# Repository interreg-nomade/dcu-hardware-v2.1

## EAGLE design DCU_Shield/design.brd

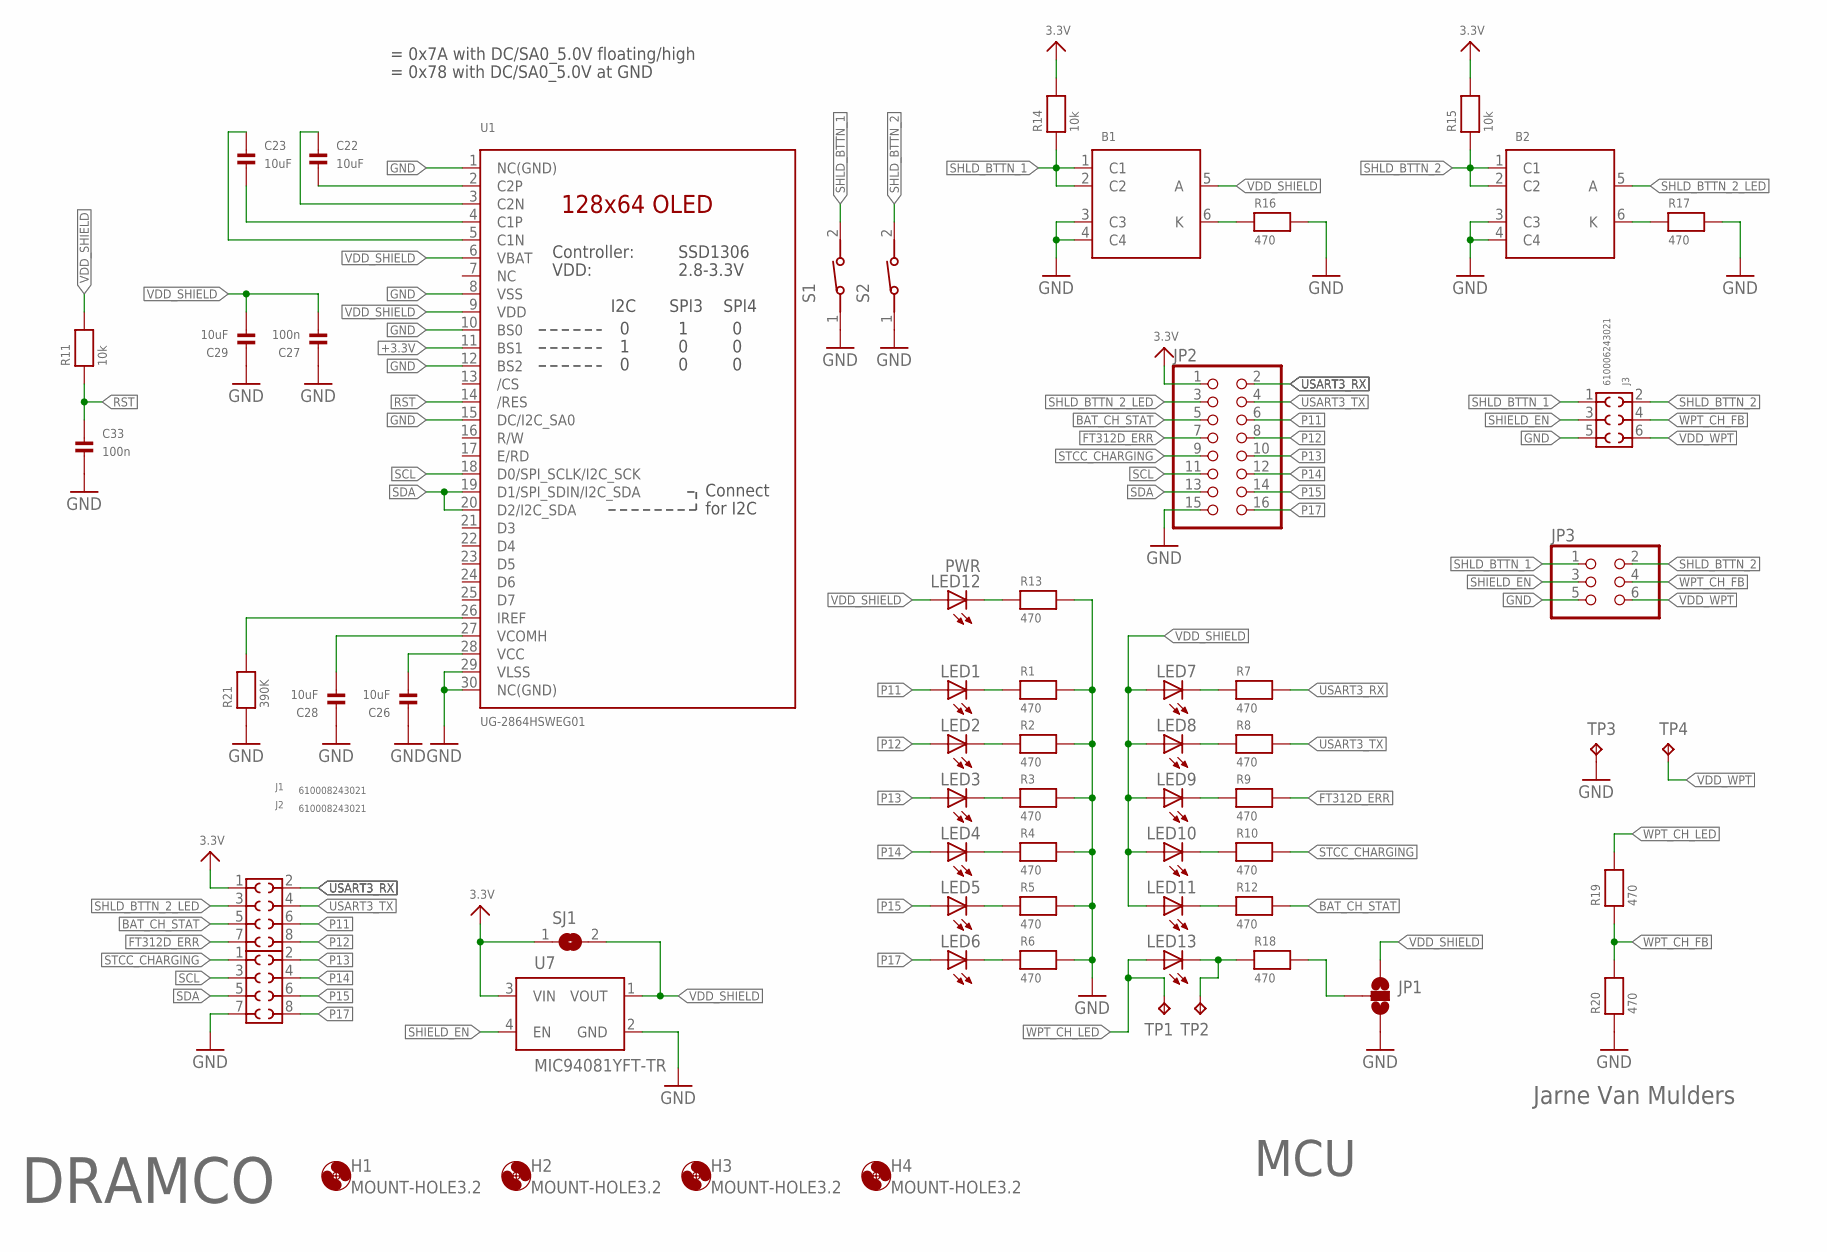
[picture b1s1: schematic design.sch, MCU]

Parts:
B1, B2: TS121273
C22, C23, C26, C28, C29: 10uF; 0805
C27, C33: 100n; 0603
H1, H2, H3, H4: MOUNT-HOLE3.2; 3,2
J1, J2: 610008243021
J3: 610006243021
JP1: JUMPER-SMT_3_NO_NO-SILK; SMT-JUMPER_3_NO_NO-SILK
JP2: HEADER-2X8; 2X08
JP3: HEADER-2X3; 2X03_ROUND_70MIL
LED1, LED2, LED3, LED4, LED5, LED6, LED7, LED8, LED9, LED10, LED11, LED13: LED3MM
LED12: PWR; LED3MM
R1, R2, R3, R4, R5, R6, R7, R8, R9, R10, R12, R13, R16, R17, R18, R19, R20: 470; 0603
R11: 10k; 0805
R14, R15: 10k; 0603
R21: 390K; 0805
S1, S2: 434111043826
SJ1: SOLDERJUMPERREFLOW; SOLDERJUMPER_REFLOW
TP1, TP2, TP3, TP4: TPTP20SQ; TP20SQ
U1: UG-2864HSWEG01; UG-2864HSWEG01_0.96IN_WRAPAROUND
U7: MIC94081YFT-TR; IC_MIC94081YFT-TR

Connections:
3.3V: J2.1, JP2.1, R14.2, R15.2, SJ1.1, U7.3 (VIN)
+3.3V: U1.11 (BS1)
BAT_CH_STAT: J2.5, JP2.5, R12.2
FT312D_ERR: J2.7, JP2.7, R9.2
GND: B1.3 (C3), B1.4 (C4), B2.3 (C3), B2.4 (C4), C26.1, C27.1, C28.1, C29.1, C33.2, J1.7, J3.5, JP1.3, JP2.15, JP3.5, R1.2, R2.2, R3.2, R4.2, R5.2, R6.2, R13.2, R16.2, R17.2, R20.1, R21.1, S1.1, S2.1, TP3.TP, U1.1 (NC(GND)), U1.8 (VSS), U1.10 (BS0), U1.12 (BS2), U1.15 (DC/I2C_SA0), U1.29 (VLSS), U1.30 (NC(GND)), U7.2 (GND)
unnamed: LED6.K (C), R6.1
unnamed: LED5.K (C), R5.1
unnamed: LED4.K (C), R4.1
unnamed: LED3.K (C), R3.1
unnamed: LED2.K (C), R2.1
unnamed: LED1.K (C), R1.1
unnamed: LED7.K (C), R7.1
unnamed: LED8.K (C), R8.1
unnamed: LED9.K (C), R9.1
unnamed: C22.2, U1.2 (C2P)
unnamed: LED10.K (C), R10.1
unnamed: LED11.K (C), R12.1
unnamed: LED12.K (C), R13.1
unnamed: B1.6 (K), R16.1
unnamed: C26.2, U1.28 (VCC)
unnamed: B2.6 (K), R17.1
unnamed: JP1.2, R18.2
unnamed: C28.2, U1.27 (VCOMH)
unnamed: LED13.K (C), R18.1, TP2.TP
unnamed: R21.2, U1.26 (IREF)
unnamed: C22.1, U1.3 (C2N)
unnamed: C23.2, U1.4 (C1P)
unnamed: C23.1, U1.5 (C1N)
P11: J2.6, JP2.6, LED1.A
P12: J2.8, JP2.8, LED2.A
P13: J1.2, JP2.10, LED3.A
P14: J1.4, JP2.12, LED4.A
P15: J1.6, JP2.14, LED5.A
P17: J1.8, JP2.16, LED6.A
RST: C33.1, R11.1, U1.14 (/RES)
SCL: J1.3, JP2.11, U1.18 (D0/SPI_SCLK/I2C_SCK)
SDA: J1.5, JP2.13, U1.19 (D1/SPI_SDIN/I2C_SDA), U1.20 (D2/I2C_SDA)
SHIELD_EN: J3.3, JP3.3, U7.4 (EN)
SHLD_BTTN_1: B1.1 (C1), B1.2 (C2), J3.1, JP3.1, R14.1, S1.2
SHLD_BTTN_2: B2.1 (C1), B2.2 (C2), J3.2, JP3.2, R15.1, S2.2
SHLD_BTTN_2_LED: B2.5 (A), J2.3, JP2.3
STCC_CHARGING: J1.1, JP2.9, R10.2
USART3_RX: J2.2, JP2.2, R7.2
USART3_TX: J2.4, JP2.4, R8.2
VDD_SHIELD: B1.5 (A), C27.2, C29.2, JP1.1, LED7.A, LED8.A, LED9.A, LED10.A, LED11.A, LED12.A, R11.2, SJ1.2, U1.6 (VBAT), U1.9 (VDD), U7.1 (VOUT)
VDD_WPT: J3.6, JP3.6, TP4.TP
WPT_CH_FB: J3.4, JP3.4, R19.1, R20.2
WPT_CH_LED: LED13.A, R19.2, TP1.TP

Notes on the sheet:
MCU
Jarne Van Mulders
DRAMCO
= 0x7A with DC/SA0_5.0V floating/high
= 0x78 with DC/SA0_5.0V at GND

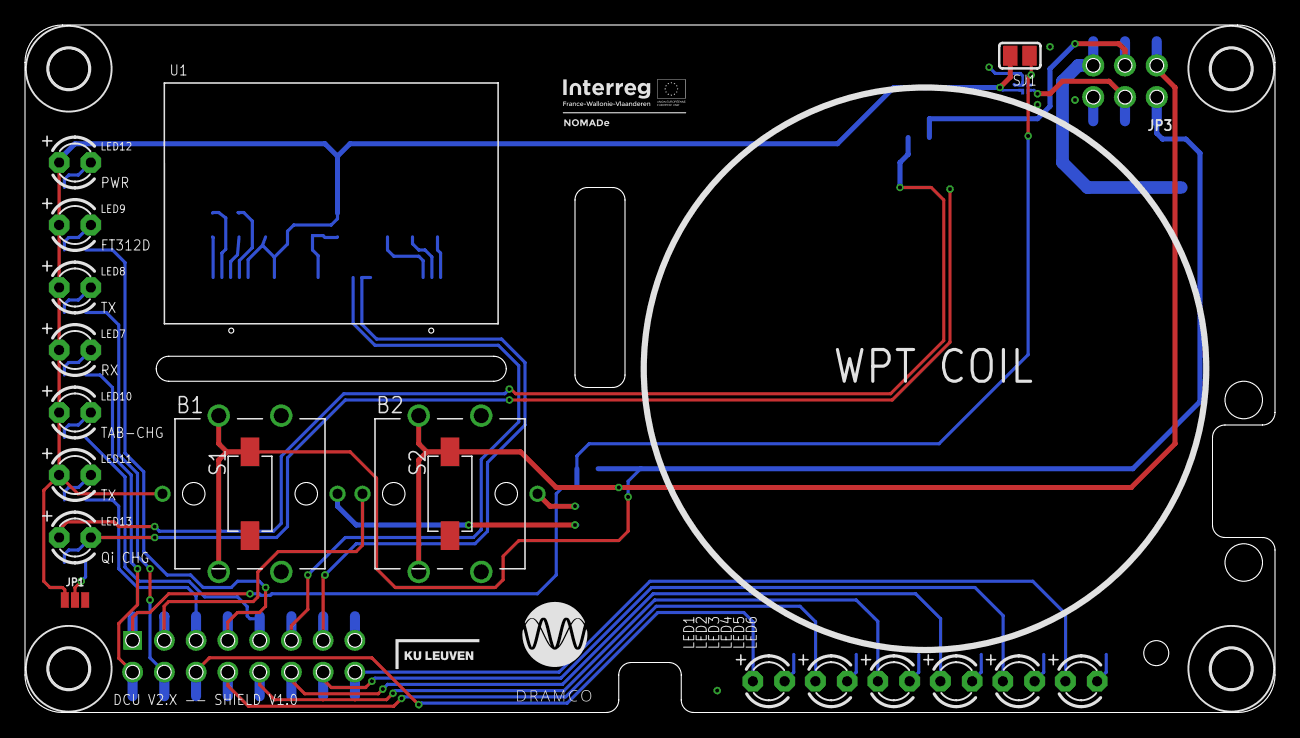
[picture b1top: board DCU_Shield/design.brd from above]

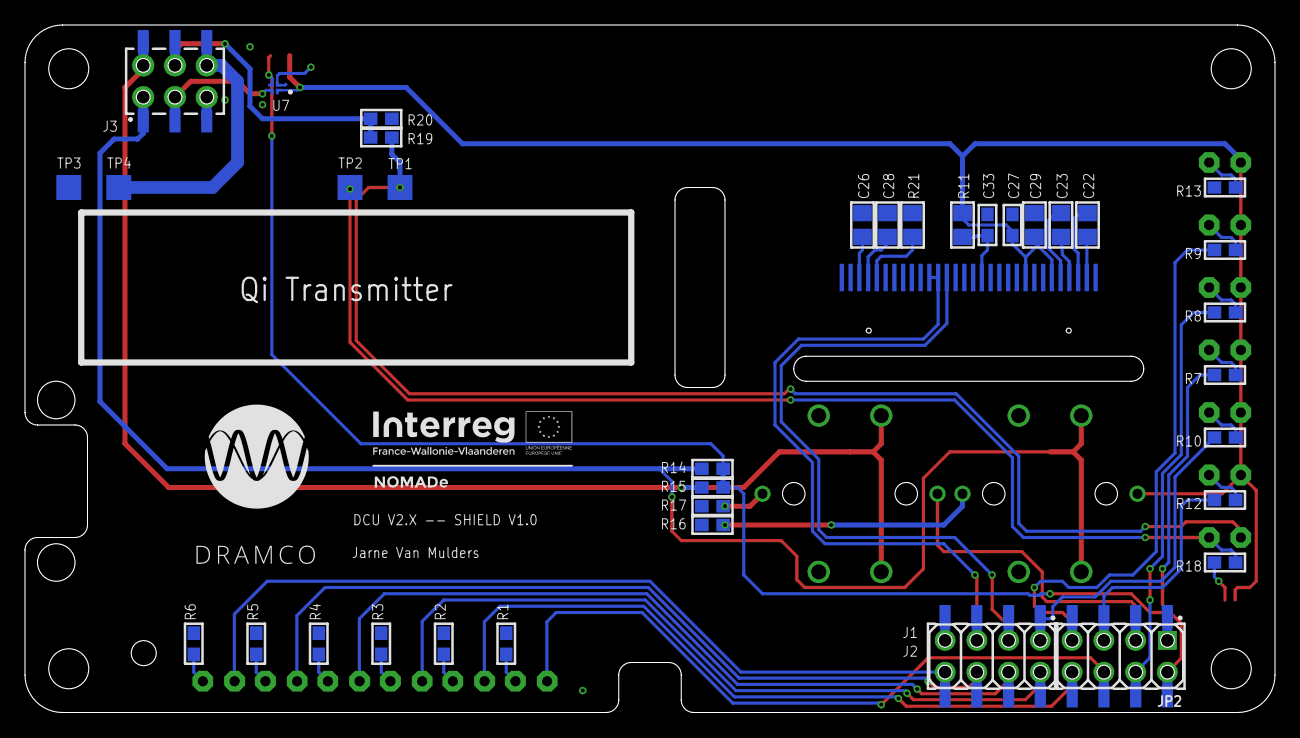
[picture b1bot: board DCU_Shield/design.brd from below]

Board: 2 copper layers, 100.0 x 55.0 mm, 62 parts (37 on the bottom side), 47 nets.

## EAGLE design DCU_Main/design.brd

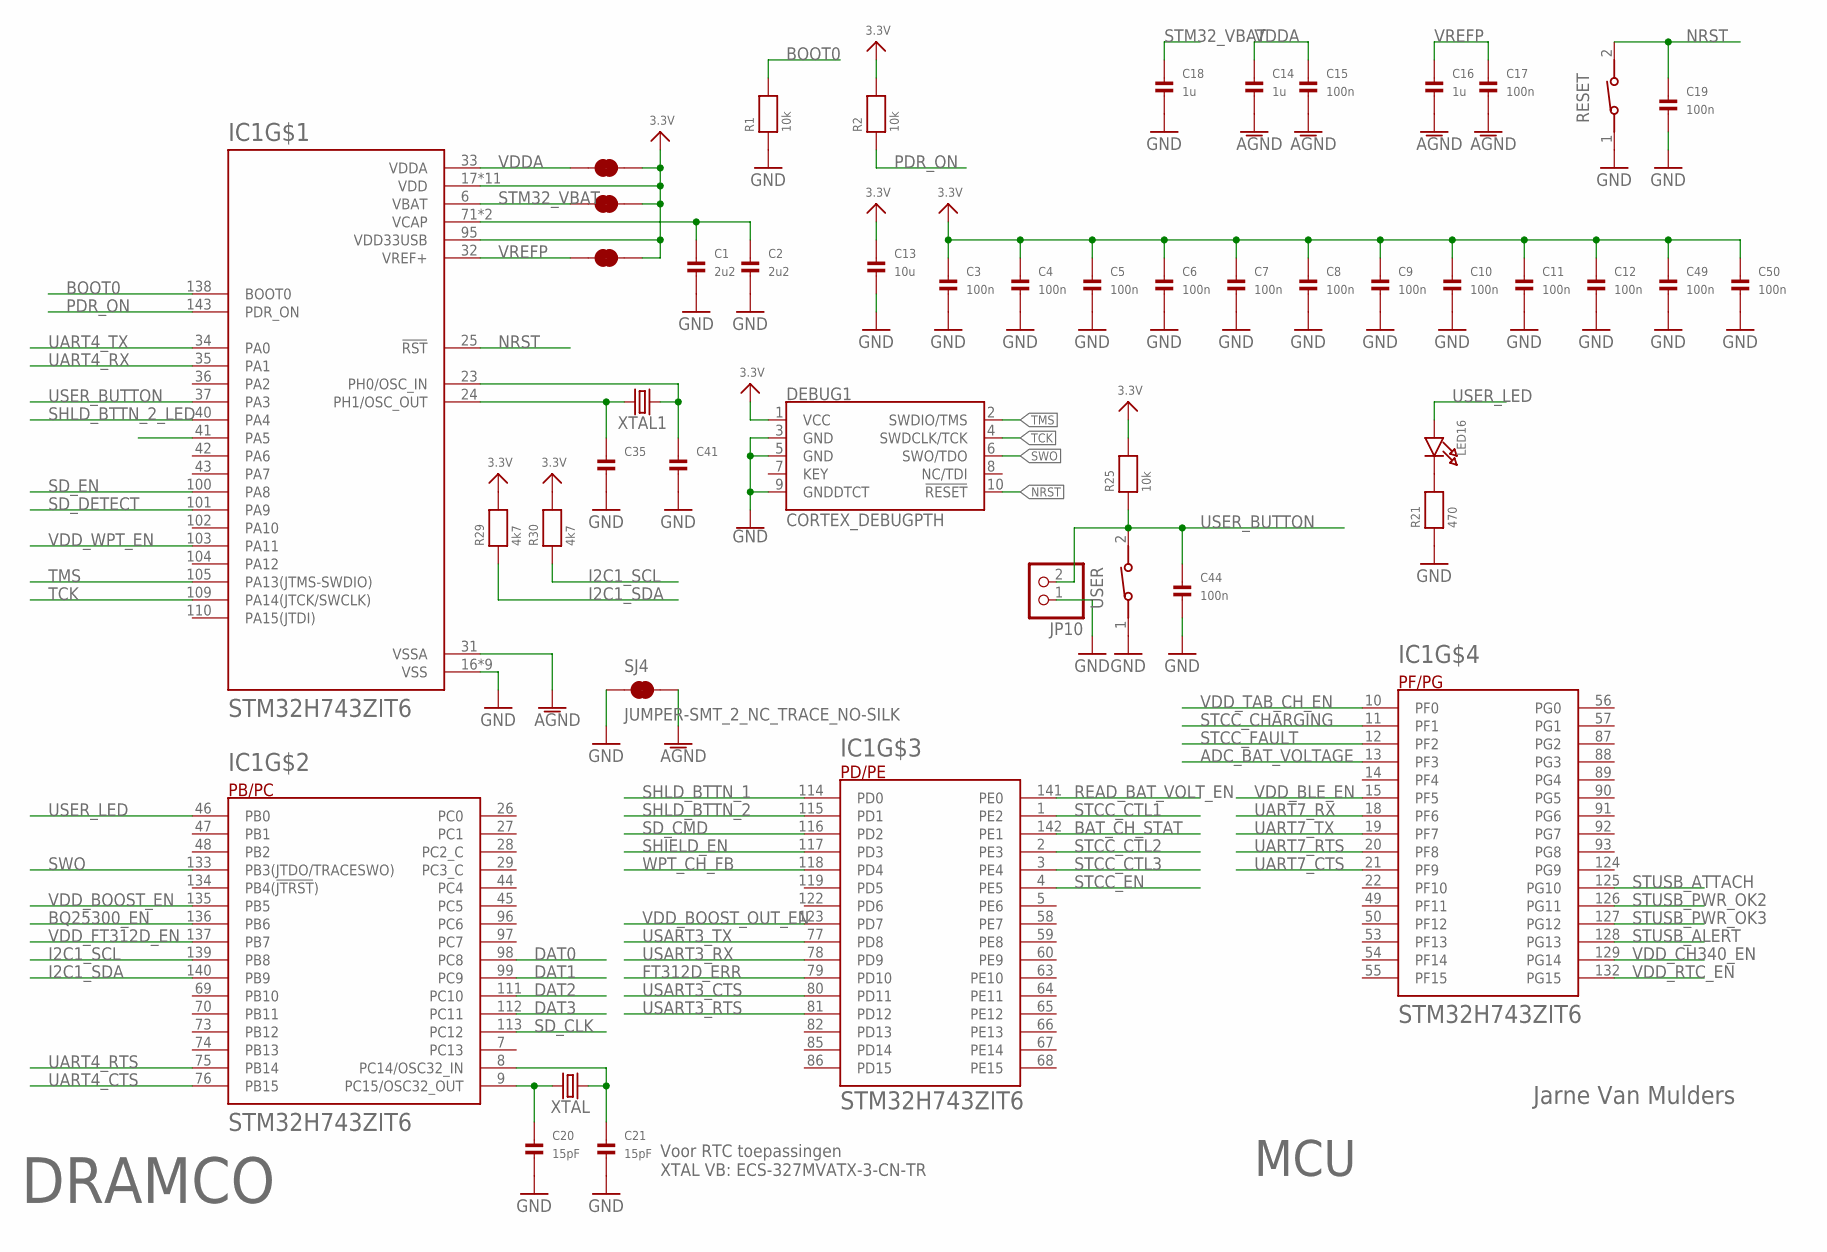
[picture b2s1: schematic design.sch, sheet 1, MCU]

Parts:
C1, C2: 2u2; 0805
C3, C4, C5, C6, C7, C8, C9, C10, C11, C12, C15, C17, C19, C44, C49, C50: 100n; 0603
C13: 10u; 0805
C14, C16, C18: 1u; 0603
C20, C21: 15pF; 0603
C35, C41: CAP_CERAMIC0603; 0603
DEBUG1: CORTEX_DEBUGPTH; 2X5-PTH-1.27MM
IC1: STM32H743ZIT6; QFP50P2200X2200X160-144N
JP10: HEADER-1X2ROUND; 1X02_ROUND
LED16: LED0805; CHIPLED_0805
R1, R2, R25: 10k; 0603
R21: 470; 0603
R29, R30: 4k7; 0603
RESET: 434111043826
SJ1, SJ2, SJ3, SJ4: JUMPER-SMT_2_NC_TRACE_NO-SILK; SMT-JUMPER_2_NC_TRACE_NO-SILK
USER: 434111043826
XTAL, XTAL1: CRYSTALSMD-3.2X2.5; CRYSTAL-SMD-3.2X2.5MM

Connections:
3.3V: C3.1, C4.1, C5.1, C6.1, C7.1, C8.1, C9.1, C10.1, C11.1, C12.1, C13.1, C49.1, C50.1, DEBUG1.1 (VCC), IC1.17 (VDD), IC1.30 (VDD), IC1.39 (VDD), IC1.52 (VDD), IC1.62 (VDD), IC1.72 (VDD), IC1.84 (VDD), IC1.95 (VDD33USB), IC1.108 (VDD), IC1.121 (VDD), IC1.131 (VDD), IC1.144 (VDD), R2.2, R25.2, R29.2, R30.2, SJ1.2, SJ2.2, SJ3.2; also elsewhere on the board
ADC_BAT_VOLTAGE: IC1.13 (PF3); also elsewhere on the board
AGND: C14.2, C15.2, C16.2, C17.2, IC1.31 (VSSA), SJ4.2
BAT_CH_STAT: IC1.142 (PE1); also elsewhere on the board
BOOT0: IC1.138 (BOOT0), R1.2
BQ25300_EN: IC1.136 (PB6); also elsewhere on the board
DAT0: IC1.98 (PC8); also elsewhere on the board
DAT1: IC1.99 (PC9); also elsewhere on the board
DAT2: IC1.111 (PC10); also elsewhere on the board
DAT3: IC1.112 (PC11); also elsewhere on the board
FT312D_ERR: IC1.79 (PD10); also elsewhere on the board
GND: C1.2, C2.2, C3.2, C4.2, C5.2, C6.2, C7.2, C8.2, C9.2, C10.2, C11.2, C12.2, C13.2, C18.2, C19.2, C20.2, C21.2, C35.2, C41.2, C44.2, C49.2, C50.2, DEBUG1.3 (GND), DEBUG1.5 (GND), DEBUG1.9 (GNDDTCT), IC1.16 (VSS), IC1.38 (VSS), IC1.51 (VSS), IC1.61 (VSS), IC1.83 (VSS), IC1.94 (VSS), IC1.107 (VSS), IC1.120 (VSS), IC1.130 (VSS), JP10.1, R1.1, R21.1, RESET.1, SJ4.1, USER.1; also elsewhere on the board
I2C1_SCL: IC1.139 (PB8), R30.1; also elsewhere on the board
I2C1_SDA: IC1.140 (PB9), R29.1; also elsewhere on the board
unnamed: C1.1, C2.1, IC1.71 (VCAP), IC1.106 (VCAP)
unnamed: C20.1, IC1.9 (PC15/OSC32_OUT), XTAL.3 (2)
unnamed: C21.1, IC1.8 (PC14/OSC32_IN), XTAL.1
unnamed: LED16.C, R21.2
unnamed: C35.1, IC1.24 (PH1/OSC_OUT), XTAL1.3 (2)
unnamed: C41.1, IC1.23 (PH0/OSC_IN), XTAL1.1
NRST: C19.1, DEBUG1.10 (!RESET), IC1.25 (!RST), RESET.2
PDR_ON: IC1.143 (PDR_ON), R2.1
READ_BAT_VOLT_EN: IC1.141 (PE0); also elsewhere on the board
SD_CLK: IC1.113 (PC12); also elsewhere on the board
SD_CMD: IC1.116 (PD2); also elsewhere on the board
SD_DETECT: IC1.101 (PA9); also elsewhere on the board
SD_EN: IC1.100 (PA8); also elsewhere on the board
SHIELD_EN: IC1.117 (PD3); also elsewhere on the board
SHLD_BTTN_1: IC1.114 (PD0); also elsewhere on the board
SHLD_BTTN_2: IC1.115 (PD1); also elsewhere on the board
SHLD_BTTN_2_LED: IC1.40 (PA4); also elsewhere on the board
STCC_CHARGING: IC1.11 (PF1); also elsewhere on the board
STCC_CTL1: IC1.1 (PE2); also elsewhere on the board
STCC_CTL2: IC1.2 (PE3); also elsewhere on the board
STCC_CTL3: IC1.3 (PE4); also elsewhere on the board
STCC_EN: IC1.4 (PE5); also elsewhere on the board
STCC_FAULT: IC1.12 (PF2); also elsewhere on the board
STM32_VBAT: C18.1, IC1.6 (VBAT), SJ2.1
STUSB_ALERT: IC1.128 (PG13); also elsewhere on the board
STUSB_ATTACH: IC1.125 (PG10); also elsewhere on the board
STUSB_PWR_OK2: IC1.126 (PG11); also elsewhere on the board
STUSB_PWR_OK3: IC1.127 (PG12); also elsewhere on the board
SWO: DEBUG1.6 (SWO/TDO), IC1.133 (PB3(JTDO/TRACESWO))
TCK: DEBUG1.4 (SWDCLK/TCK), IC1.109 (PA14(JTCK/SWCLK))
TMS: DEBUG1.2 (SWDIO/TMS), IC1.105 (PA13(JTMS-SWDIO))
UART4_CTS: IC1.76 (PB15); also elsewhere on the board
UART4_RTS: IC1.75 (PB14); also elsewhere on the board
UART4_RX: IC1.35 (PA1); also elsewhere on the board
UART4_TX: IC1.34 (PA0); also elsewhere on the board
UART7_CTS: IC1.21 (PF9); also elsewhere on the board
UART7_RTS: IC1.20 (PF8); also elsewhere on the board
UART7_RX: IC1.18 (PF6); also elsewhere on the board
UART7_TX: IC1.19 (PF7); also elsewhere on the board
USART3_CTS: IC1.80 (PD11); also elsewhere on the board
USART3_RTS: IC1.81 (PD12); also elsewhere on the board
USART3_RX: IC1.78 (PD9); also elsewhere on the board
USART3_TX: IC1.77 (PD8); also elsewhere on the board
USER_BUTTON: C44.1, IC1.37 (PA3), JP10.2, R25.1, USER.2
USER_LED: IC1.46 (PB0), LED16.A
VDDA: C14.1, C15.1, IC1.33 (VDDA), SJ3.1
VDD_BLE_EN: IC1.15 (PF5); also elsewhere on the board
VDD_BOOST_EN: IC1.135 (PB5); also elsewhere on the board
VDD_BOOST_OUT_EN: IC1.123 (PD7); also elsewhere on the board
VDD_CH340_EN: IC1.129 (PG14); also elsewhere on the board
VDD_FT312D_EN: IC1.137 (PB7); also elsewhere on the board
VDD_NRF_EN: IC1.41 (PA5)
VDD_RTC_EN: IC1.132 (PG15); also elsewhere on the board
VDD_TAB_CH_EN: IC1.10 (PF0); also elsewhere on the board
VDD_WPT_EN: IC1.103 (PA11); also elsewhere on the board
VREFP: C16.1, C17.1, IC1.32 (VREF+), SJ1.1
WPT_CH_FB: IC1.118 (PD4); also elsewhere on the board

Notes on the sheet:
Voor RTC toepassingen XTAL VB: ECS-327MVATX-3-CN-TR
MCU
Jarne Van Mulders
DRAMCO

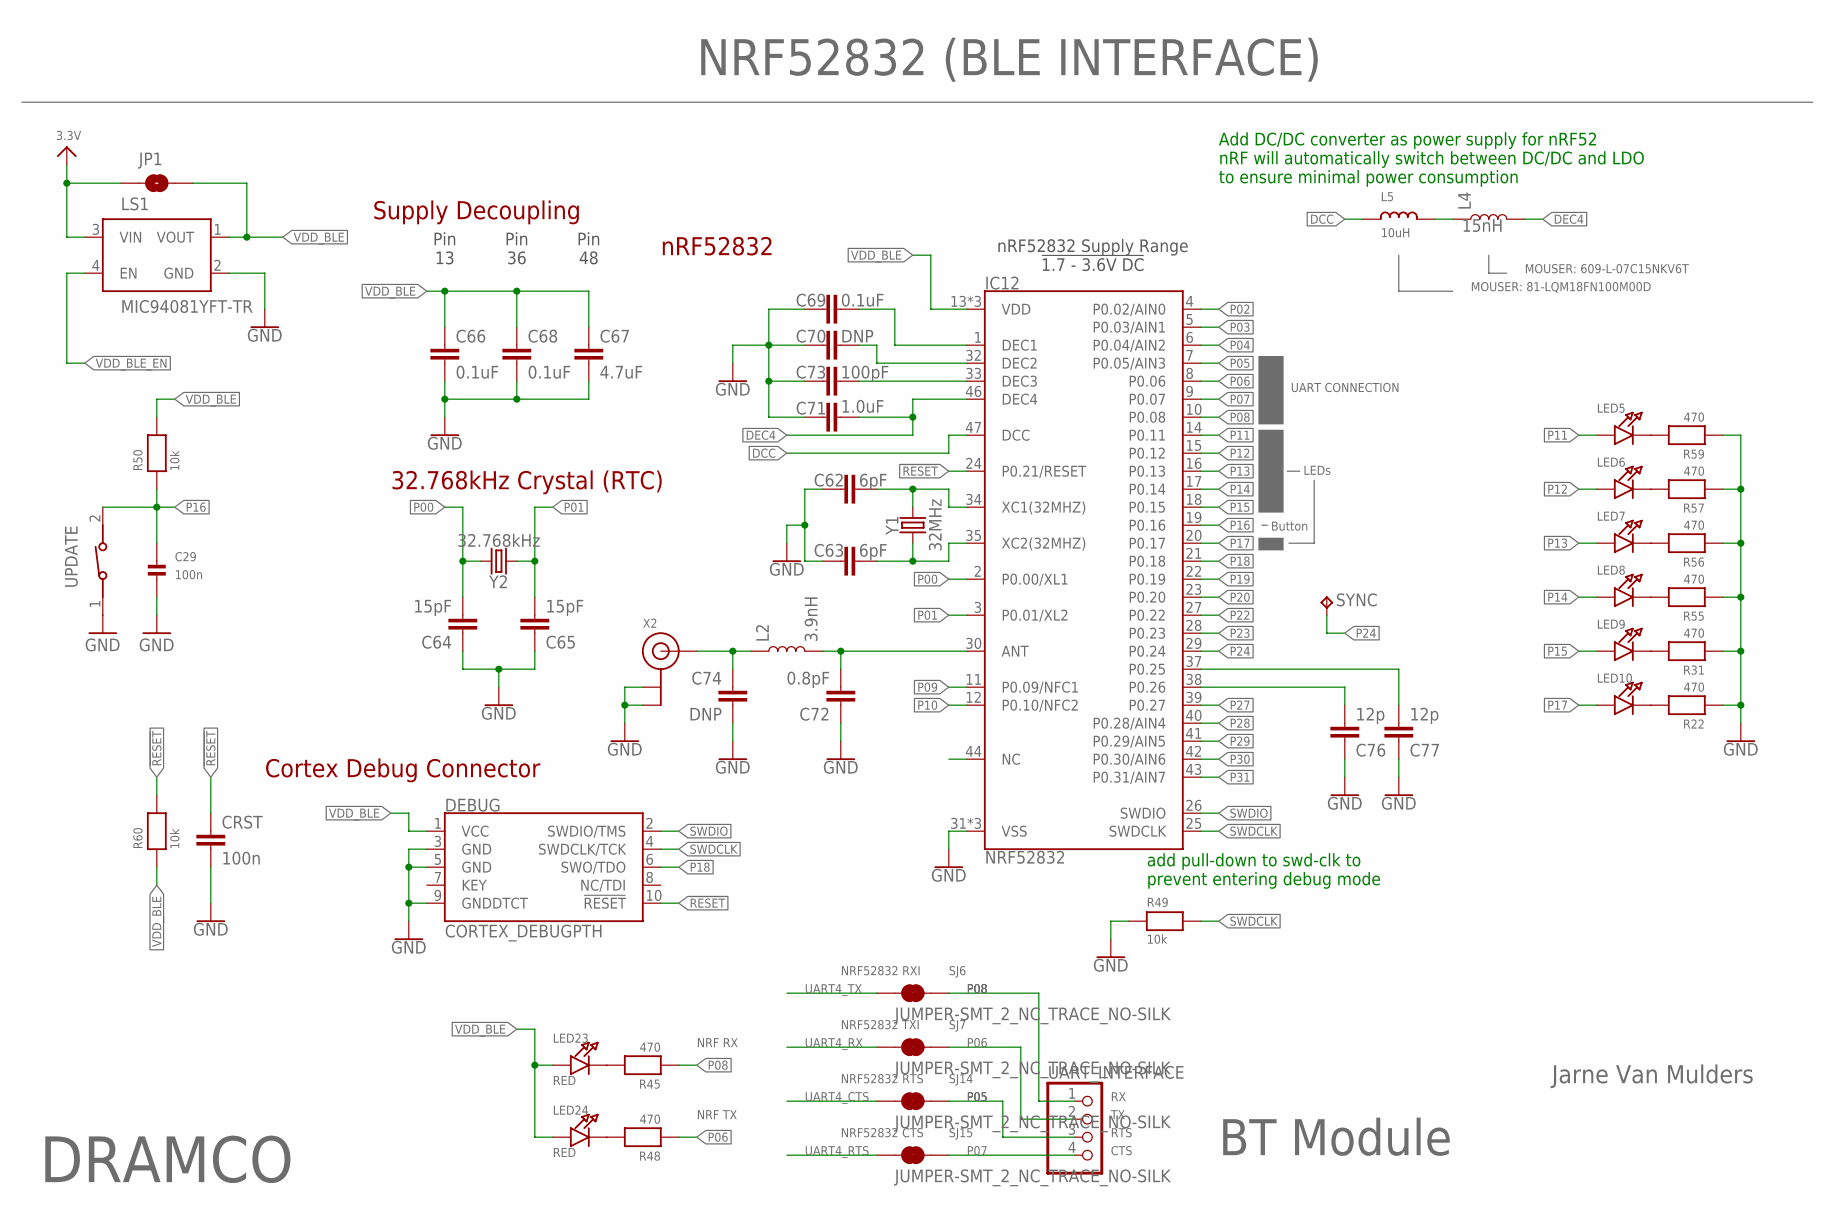
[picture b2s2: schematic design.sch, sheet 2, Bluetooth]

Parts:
C29: 100n; 0603
C62, C63: 6pF; 0402
C64, C65: 15pF; 0402
C66, C68, C69: 0.1uF; 0402
C67: 4.7uF; 0603
C70, C74: DNP; 0402
C71: 1.0uF; 0402
C72: 0.8pF; 0402
C73: 100pF; 0402
C76, C77: 12p; 0402
CRST: 100n; C0603
DEBUG: CORTEX_DEBUGPTH; 2X5-PTH-1.27MM
IC12: NRF52832; QFN48-6X6MM
JP1: JUMPER-SMT_2_NO_NO-SILK; SMT-JUMPER_2_NO_NO-SILK
L2: 3.9nH; 0402
L4: 15nH; 0402
L5: 10uH; _0603MP
LED5, LED6, LED7, LED8, LED9, LED10: LED0805; CHIPLED_0805
LED23, LED24: RED; CHIPLED_0805
LS1: MIC94081YFT-TR; IC_MIC94081YFT-TR
R22, R31, R45, R48, R55, R56, R57, R59: 470; 0603
R49, R50, R60: 10k; 0603
SJ6, SJ7, SJ14, SJ15: JUMPER-SMT_2_NC_TRACE_NO-SILK; SMT-JUMPER_2_NC_TRACE_NO-SILK
SYNC: TPTP09R; TP09R
UART_INTERFACE: HEADER-1X4ROUND; 1X04_ROUND
UPDATE: 434111043826
X2: ANTENNA_U.FL; U.FL
Y1: 32MHz; CRYSTAL-SMD-2.0X1.6MM
Y2: 32.768kHz; CRYSTAL-SMD-3.2X1.5MM

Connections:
3.3V: JP1.1, LS1.3 (VIN); also elsewhere on the board
!RESET!: CRST.1, DEBUG.10 (!RESET), IC12.24 (P0.21/RESET), R60.2
ANT: C72.2, IC12.30 (ANT), L2.2
DCC: IC12.47 (DCC), L5.1
DEC4: C71.2, IC12.46 (DEC4), L4.2
DEC5: C69.2, IC12.1 (DEC1)
DEC6: C70.2, IC12.32 (DEC2)
DEC8: C73.2, IC12.33 (DEC3)
GND: C29.2, C62.1, C63.2, C64.1, C65.1, C66.2, C67.2, C68.2, C69.1, C70.1, C71.1, C72.1, C73.1, C74.2, C76.1, C77.1, CRST.2, DEBUG.3 (GND), DEBUG.5 (GND), DEBUG.9 (GNDDTCT), IC12.31 (VSS), IC12.45 (VSS), IC12.EP (VSS), LS1.2 (GND), R22.1, R31.1, R49.1, R55.1, R56.1, R57.1, R59.1, UPDATE.1, X2.1 (GND), X2.2 (GND); also elsewhere on the board
unnamed: LED10.C, R22.2
unnamed: LED9.C, R31.2
unnamed: LED8.C, R55.2
unnamed: C74.1, L2.1, X2.3 (SIGNAL)
unnamed: LED7.C, R56.2
unnamed: LED6.C, R57.2
unnamed: LED23.C, R45.2
unnamed: C77.2, IC12.37 (P0.25)
unnamed: LED24.C, R48.2
unnamed: L4.1, L5.2
unnamed: LED5.C, R59.2
NC: IC12.44 (NC)
P00: C64.2, IC12.2 (P0.00/XL1), Y2.P$2 (2)
P01: C65.2, IC12.3 (P0.01/XL2), Y2.P$1 (1)
P02: IC12.4 (P0.02/AIN0)
P03: IC12.5 (P0.03/AIN1)
P04: IC12.6 (P0.04/AIN2)
P05: IC12.7 (P0.05/AIN3), SJ14.2, UART_INTERFACE.3
P06: IC12.8 (P0.06), R48.1, SJ7.2, UART_INTERFACE.2
P07: IC12.9 (P0.07), SJ15.2, UART_INTERFACE.4
P08: IC12.10 (P0.08), R45.1, SJ6.2, UART_INTERFACE.1
P09: IC12.11 (P0.09/NFC1)
P10: IC12.12 (P0.10/NFC2)
P11: IC12.14 (P0.11), LED5.A; also elsewhere on the board
P12: IC12.15 (P0.12), LED6.A; also elsewhere on the board
P13: IC12.16 (P0.13), LED7.A; also elsewhere on the board
P14: IC12.17 (P0.14), LED8.A; also elsewhere on the board
P15: IC12.18 (P0.15), LED9.A; also elsewhere on the board
P16: C29.1, IC12.19 (P0.16), R50.1, UPDATE.2
P17: IC12.20 (P0.17), LED10.A; also elsewhere on the board
P18: DEBUG.6 (SWO/TDO), IC12.21 (P0.18)
P19: IC12.22 (P0.19)
P20: IC12.23 (P0.20)
P22: IC12.27 (P0.22)
P23: IC12.28 (P0.23)
P24: IC12.29 (P0.24), SYNC.TP
P26: C76.2, IC12.38 (P0.26)
P27: IC12.39 (P0.27)
P28: IC12.40 (P0.28/AIN4)
P29: IC12.41 (P0.29/AIN5)
P30: IC12.42 (P0.30/AIN6)
P31: IC12.43 (P0.31/AIN7)
SWDCLK: DEBUG.4 (SWDCLK/TCK), IC12.25 (SWDCLK), R49.2
SWDIO: DEBUG.2 (SWDIO/TMS), IC12.26 (SWDIO)
UART4_CTS: SJ14.1; also elsewhere on the board
UART4_RTS: SJ15.1; also elsewhere on the board
UART4_RX: SJ7.1; also elsewhere on the board
UART4_TX: SJ6.1; also elsewhere on the board
VDD_BLE: C66.1, C67.1, C68.1, DEBUG.1 (VCC), IC12.13 (VDD), IC12.36 (VDD), IC12.48 (VDD), JP1.2, LED23.A, LED24.A, LS1.1 (VOUT), R50.2, R60.1
VDD_BLE_EN: LS1.4 (EN); also elsewhere on the board
XC1: C62.2, IC12.34 (XC1(32MHZ)), Y1.3 (2)
XC2: C63.1, IC12.35 (XC2(32MHZ)), Y1.1

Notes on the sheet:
BT Module
Jarne Van Mulders
DRAMCO
NRF52832 (BLE INTERFACE)
Pin 13
Pin 36
Pin 48
nRF52832
32.768kHz Crystal (RTC)
Supply Decoupling
Cortex Debug Connector
nRF52832 Supply Range !1.7 - 3.6V DC!
Add DC/DC converter as power supply for nRF52 nRF will automatically switch between DC/DC and LDO to ensure minimal power consumption
add pull-down to swd-clk to prevent entering debug mode
NRF52832 RXI
NRF52832 TXI
NRF52832 RTS
NRF52832 CTS
MOUSER: 81-LQM18FN100M00D
MOUSER: 609-L-07C15NKV6T
NRF RX
NRF TX
RTS
CTS
UART CONNECTION
LEDs
Button

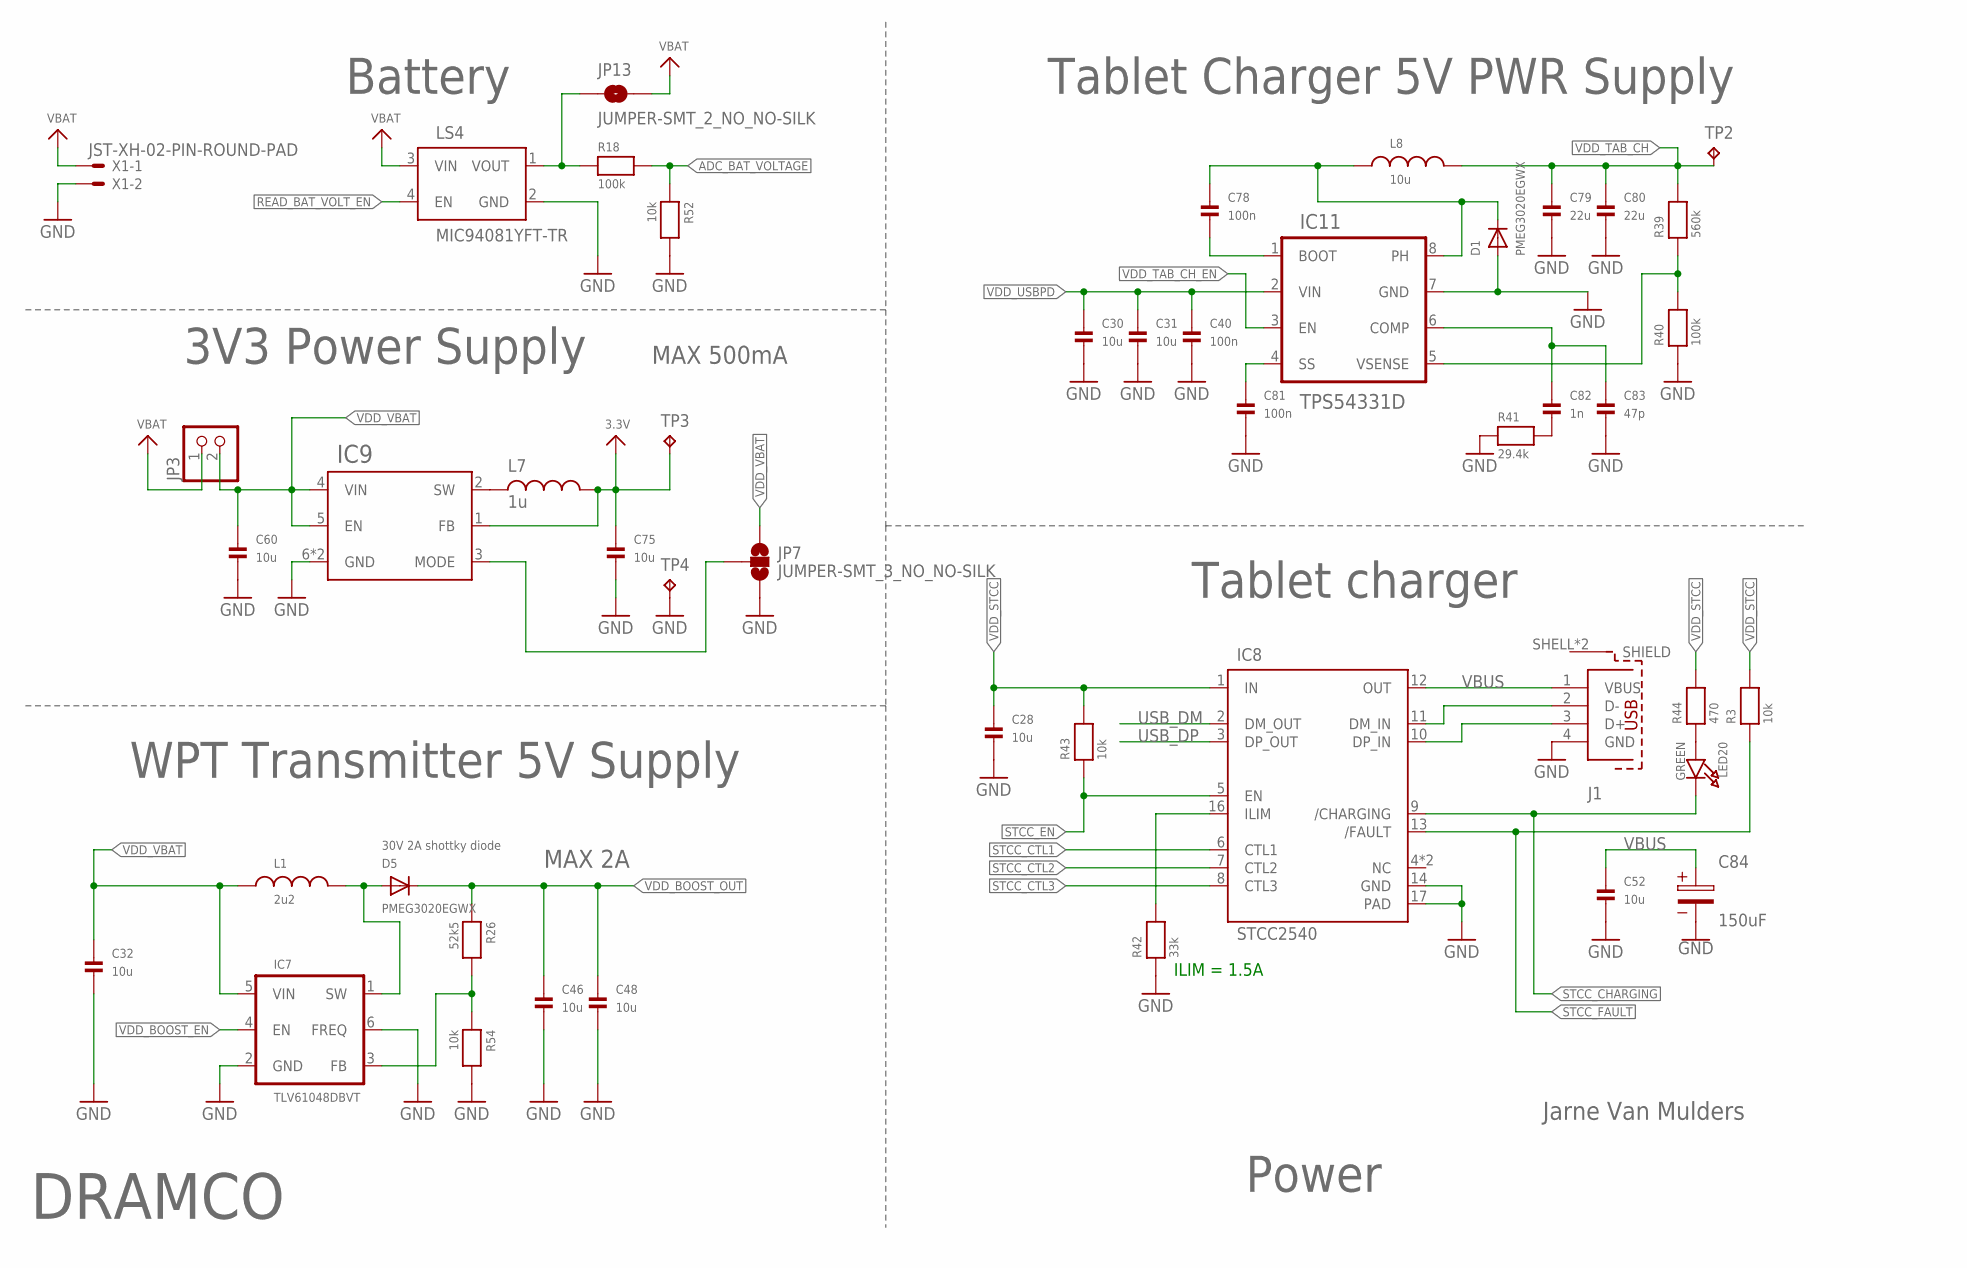
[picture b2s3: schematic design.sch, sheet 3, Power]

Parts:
C28, C32, C46, C48, C52, C60, C75: 10u; 0805
C30, C31: 10u; 1206
C40, C81: 100n; 0603
C78: 100n; 0402
C79, C80: 22u; 0805
C82: 1n; 0603
C83: 47p; 0603
C84: 150uF; 3.5X1.6X2.1(BXCXA)
D1, D5: PMEG3020EGWX; SOD-123
IC7: TLV61048DBVT; SOT95P280X145-6N
IC8: STCC2540; QFN50P300X300X80-17N
IC9: FAN5362UMP33X; MLF-8
IC11: TPS54331D; SOIC127P599X175-8N
J1: 614004190021
JP3: HEADER-1X2ROUND; 1X02_ROUND
JP7: JUMPER-SMT_3_NO_NO-SILK; SMT-JUMPER_3_NO_NO-SILK
JP13: JUMPER-SMT_2_NO_NO-SILK; SMT-JUMPER_2_NO_NO-SILK
L1: 2u2; WE-MAIA_3020
L7: 1u; WE-MAIA_2506
L8: 10u; WE-MAIA_4030
LED20: GREEN; CHIPLED_0805
LS4: MIC94081YFT-TR; IC_MIC94081YFT-TR
R3, R43, R52, R54: 10k; 0603
R18, R40: 100k; 0603
R26: 52k5; 0603
R39: 560k; 0603
R41: 29.4k; 0603
R42: 33k; 0603
R44: 470; 0603
TP2, TP3, TP4: TPTP10R; TP10R
X1: JST-XH-02-PIN-ROUND-PAD; JST-XH-02-PACKAGE-ROUND-PAD

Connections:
3.3V: C75.1, IC9.1 (FB), L7.2, TP3.TP; also elsewhere on the board
ADC_BAT_VOLTAGE: R18.2, R52.1; also elsewhere on the board
GND: C28.2, C30.2, C31.2, C32.2, C40.2, C46.2, C48.2, C52.2, C60.2, C75.2, C79.2, C80.2, C81.2, C83.2, C84.2, D1.A, IC7.2 (GND), IC7.6 (FREQ), IC8.14 (GND), IC8.17 (PAD), IC9.6 (GND), IC9.7 (GND), IC11.7 (GND), J1.4 (GND), JP7.3, LS4.2 (GND), R40.1, R41.1, R42.1, R52.2, R54.2, TP4.TP, X1.2; also elsewhere on the board
unnamed: LED20.A, R44.1
unnamed: IC9.2 (SW), L7.1
unnamed: C78.1, D1.C, IC11.8 (PH), L8.1
unnamed: D5.A, IC7.1 (SW), L1.2
unnamed: IC8.16 (ILIM), R42.2
unnamed: JP13.1, LS4.1 (VOUT), R18.1
unnamed: C81.1, IC11.4 (SS)
unnamed: IC7.3 (FB), R26.2, R54.1
unnamed: C78.2, IC11.1 (BOOT)
unnamed: IC8.11 (DM_IN), J1.2 (D-)
unnamed: IC8.10 (DP_IN), J1.3 (D+)
unnamed: C82.1, C83.1, IC11.6 (COMP)
unnamed: IC11.5 (VSENSE), R39.1, R40.2
unnamed: C82.2, R41.2
unnamed: IC9.3 (MODE), JP7.2
READ_BAT_VOLT_EN: LS4.4 (EN); also elsewhere on the board
STCC_CHARGING: IC8.9 (/CHARGING), LED20.C; also elsewhere on the board
STCC_CTL1: IC8.6 (CTL1); also elsewhere on the board
STCC_CTL2: IC8.7 (CTL2); also elsewhere on the board
STCC_CTL3: IC8.8 (CTL3); also elsewhere on the board
STCC_EN: IC8.5 (EN), R43.1; also elsewhere on the board
STCC_FAULT: IC8.13 (/FAULT), R3.1; also elsewhere on the board
USB_DM: IC8.2 (DM_OUT); also elsewhere on the board
USB_DP: IC8.3 (DP_OUT); also elsewhere on the board
VBAT: JP3.1, JP13.2, LS4.3 (VIN), X1.1; also elsewhere on the board
VBUS: C52.1, C84.1, IC8.12 (OUT), J1.1 (VBUS)
VDD_BOOST_EN: IC7.4 (EN); also elsewhere on the board
VDD_BOOST_OUT: C46.1, C48.1, D5.C, R26.1; also elsewhere on the board
VDD_STCC: C28.1, IC8.1 (IN), R3.2, R43.2, R44.2; also elsewhere on the board
VDD_TAB_CH: C79.1, C80.1, L8.2, R39.2, TP2.TP; also elsewhere on the board
VDD_TAB_CH_EN: IC11.3 (EN); also elsewhere on the board
VDD_USBPD: C30.1, C31.1, C40.1, IC11.2 (VIN); also elsewhere on the board
VDD_VBAT: C32.1, C60.1, IC7.5 (VIN), IC9.4 (VIN), IC9.5 (EN), JP3.2, JP7.1, L1.1

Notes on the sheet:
Power
Jarne Van Mulders
DRAMCO
MAX 500mA
30V 2A shottky diode
MAX 2A
3V3 Power Supply
Tablet charger
Battery
WPT Transmitter 5V Supply
Tablet Charger 5V PWR Supply
ILIM = 1.5A

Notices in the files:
parts and their libraries:
microbuilder: This work is placed in the public domain, and may be freely used for commercial and non-commercial work with the following conditions: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
SparkFun-IC-Comms: Licensing: Creative Commons ShareAlike 4.0 International - https://creativecommons.org/licenses/by-sa/4.0
